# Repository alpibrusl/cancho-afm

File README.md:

# cancho-afm

An atomic force microscope, and a high-speed one as the second goal, that **runs by itself**: the software is written in
[cancho](https://github.com/alpibrusl/cancho), the controller logic in [cancho-hdl](https://github.com/alpibrusl/cancho-hdl), the
operator interface in [cancho-ui](https://github.com/alpibrusl/cancho-ui), and the hardware is built only from open hardware.

> **Status: design. Nothing is built, nothing is measured, no part has been bought.** Everything in `docs/` is a plan or a
> reading of someone else's published work, marked as such. The build manual in `docs/manual/` is a **draft**: no step in it has
> been carried out by anyone yet, and each step says so until someone signs it off.

## What "automatic" means here

1. **Approach**: bring the tip to the surface without crashing it, with no operator at the knobs.
2. **Tune**: find the cantilever's resonance, choose the setpoint and the loop gains, and tell the operator what it chose.
3. **Scan**: raster a requested area, keep the feedback stable, stop and retract on a fault.
4. **Report**: write the image with every setting that made it, so a run can be repeated.

The safety rule of `cancho-robot` carries over: the part that can damage the instrument (the Z drive and the approach motor) sits
behind a limit and a deadman that live in hardware, so a software fault cannot drive the tip into the sample.

## Layout

| Path | What |
|---|---|
| `docs/design.md` | the architecture, what is automatic, the safety model, the slices |
| `docs/open-hardware-policy.md` | what "open hardware only" means for this project and what it excludes |
| `docs/references.md` | the open AFM/SPM projects this builds on, read from search results, not verified |
| `docs/manual/` | how to build the device (draft) |
| `docs/index.html` | the project page and the step-by-step tutorial |
| `docs/simulator.md`, `docs/host.md`, `docs/registers.md` | the software twin, the host program, the board's register map |
| `docs/amplifier.md`, `hw/amp/` | the amplifier design and its ngspice simulations |
| `docs/first-hardware.md`, `bench/` | the first run on the real board |
| `docs/cost.md`, `docs/buy-now.md` | what build one costs for France and Spain, and what to order now |
| `gen/`, `sim/`, `host/`, `tests/` | the generated hardware, the models, the host program and their tests; `sh test_all.sh` runs all of it |

Open questions are issues in this repository.

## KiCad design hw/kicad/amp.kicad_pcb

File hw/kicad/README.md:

# hw/kicad: the piezo driver board

`amp.kicad_sch` is the schematic of the X, Y and Z piezo drivers, the 1.43 V reference, the supply and the fork's front end (drive divider, C0 trimmer, transimpedance stage, gain about 1.65 V, ADC clamp) of [`docs/amplifier.md`](../../docs/amplifier.md), **generated** by `gen_sch.cho`
(`cancho run hw/kicad/gen_sch.cho --std > hw/kicad/amp.kicad_sch`). It is written like a netlist: every pin ends in a net label, so the nets are the names in the generator and nothing depends on
placement. The symbols are the generator's own (library `cancho`, embedded in the file); the footprints are the parts to buy, **not checked against their pad numbering**.

`sh hw/kicad/check.sh` (with `CANCHO` and, for the KiCad part, `KICAD_CLI`) checks: the file equals the generator's output; KiCad's ERC (10.0.7) has no finding except the library
configuration of the machine; and `check_nets.py` reads the exported netlist and confirms, for X, Y and Z, that Rf is taken from the load side, Cf from the op-amp output, Riso in series, the
op-amp pins, the values **equal those of `hw/amp/xy_amp_b.cir` and `z_amp.cir`**, the reference divider can hold 1.43 V, and the decoupling is there.

The 48 checks include the fork front end's values against `hw/amp/fork_fe.cir`, and each of three deliberate breaks (a wrong value, swapped op-amp inputs, a clamp to the wrong rail) is caught. **Not done:** no board layout; the front end is on the same ±12 V rails as the drivers (the ADC clamp, not the rail, protects the converter); no layout guard around the 1 Mohm node; part values are those
of the simulation (the piezo's capacitance and the op-amp's output resistance are still assumptions). The first check found a real error: `z_amp.cir` carried Cf = 330 pF while the design and
the document's table use 680 pF; the file is corrected.

## The board (`amp.kicad_pcb`): placed and routed, in cancho

`sh hw/kicad/make_pcb.sh > hw/kicad/amp.kicad_pcb` (with `CANCHO` and `KICAD_CLI`) makes the board end to end:

1. `gen_pcb.py` (Python, standard library only) reads the netlist exported from the schematic, copies each footprint it names from KiCad's own libraries, puts the 69 parts in rows by function, draws a 141 x 121 mm outline and a ground
   pour (solid connections) on both layers, and writes the pads to `/tmp/amprouter/pads.txt`;
2. **`route.cho` routes it, in cancho; no Java, no Freerouting.** A 127 um grid on two layers; each net grows as a tree, one pad at a time, by a shortest-path search (Dijkstra with a penalty for going against a layer's preferred
   direction and for a via) to the nearest pad it has not joined; routed copper and pads become keep-out disks for the other nets (track 0.25 mm, clearance 0.2 mm, via 0.8 mm / 0.4 mm drill, plus a cell for the snapping of
   centres to the grid). Ground is routed like the others (a pour alone left islands that KiCad reports as unconnected), and the pour is added on top. No rip-up: a blocked net is reported (`F n`) and left, so the answer is a partial routing, never a short. It runs in about 3 seconds;
3. `gen_pcb.py` adds the tracks and vias to the board.

**Result (KiCad 10.0.7 DRC, with refilled zones):** every net routed, ground included as well as poured (45 vias, from 55 in the first version; power tracks 0.5 mm; the 1 Mohm node's copper is routed early and its pads and tracks carry a 0.9 mm keep-out for other copper), **0 unconnected, 0 clearance, 0 shorting findings, 0 schematic-parity errors**; the only findings are 69 about the machine's library
configuration, ignored by `check.sh`. A deliberate short added to a copy is reported (5 shorting items), and a wrong pad net raises the parity errors, so the check can fail. Two first runs showed what the router's model got wrong,
and the fixes are in the source: pad keep-outs ignored the snapping of centres to the grid (clearance 0.17 mm against 0.2 mm), and a square pad reaches its corner, not its half-width.

**The 1 Mohm node (TIN), measured on the routed board, not gated:** the smallest gap between its copper and any other net's copper is **0.43 mm**, not the 0.9 mm asked for. The keep-out works one way (other nets keep 0.9 mm from TIN's tracks and pads), but TIN's own tracks were only kept the ordinary 0.2 mm from other nets' pads, and those pads set the 0.43 mm. It is a keep-out plus the ground pour around it, **not a driven guard ring**. Do not read it as leakage-safe: that needs a guard at the input potential (here a virtual ground, so ground itself) and a clean board.

**Not done, and not claimed:** the placement is a first arrangement, not an optimised one (45 vias is still a lot; the op-amps' decoupling loops are not short by design; the piezo outputs are not kept away
from the fork input); the tracks are 90 degrees (no 45-degree corners), power tracks 0.5 mm and the rest 0.25 mm; no mounting holes or silkscreen text; no fabrication check (a fab's own rules, the stack-up, annular ring, drill sizes); and the
board has never been built or measured.

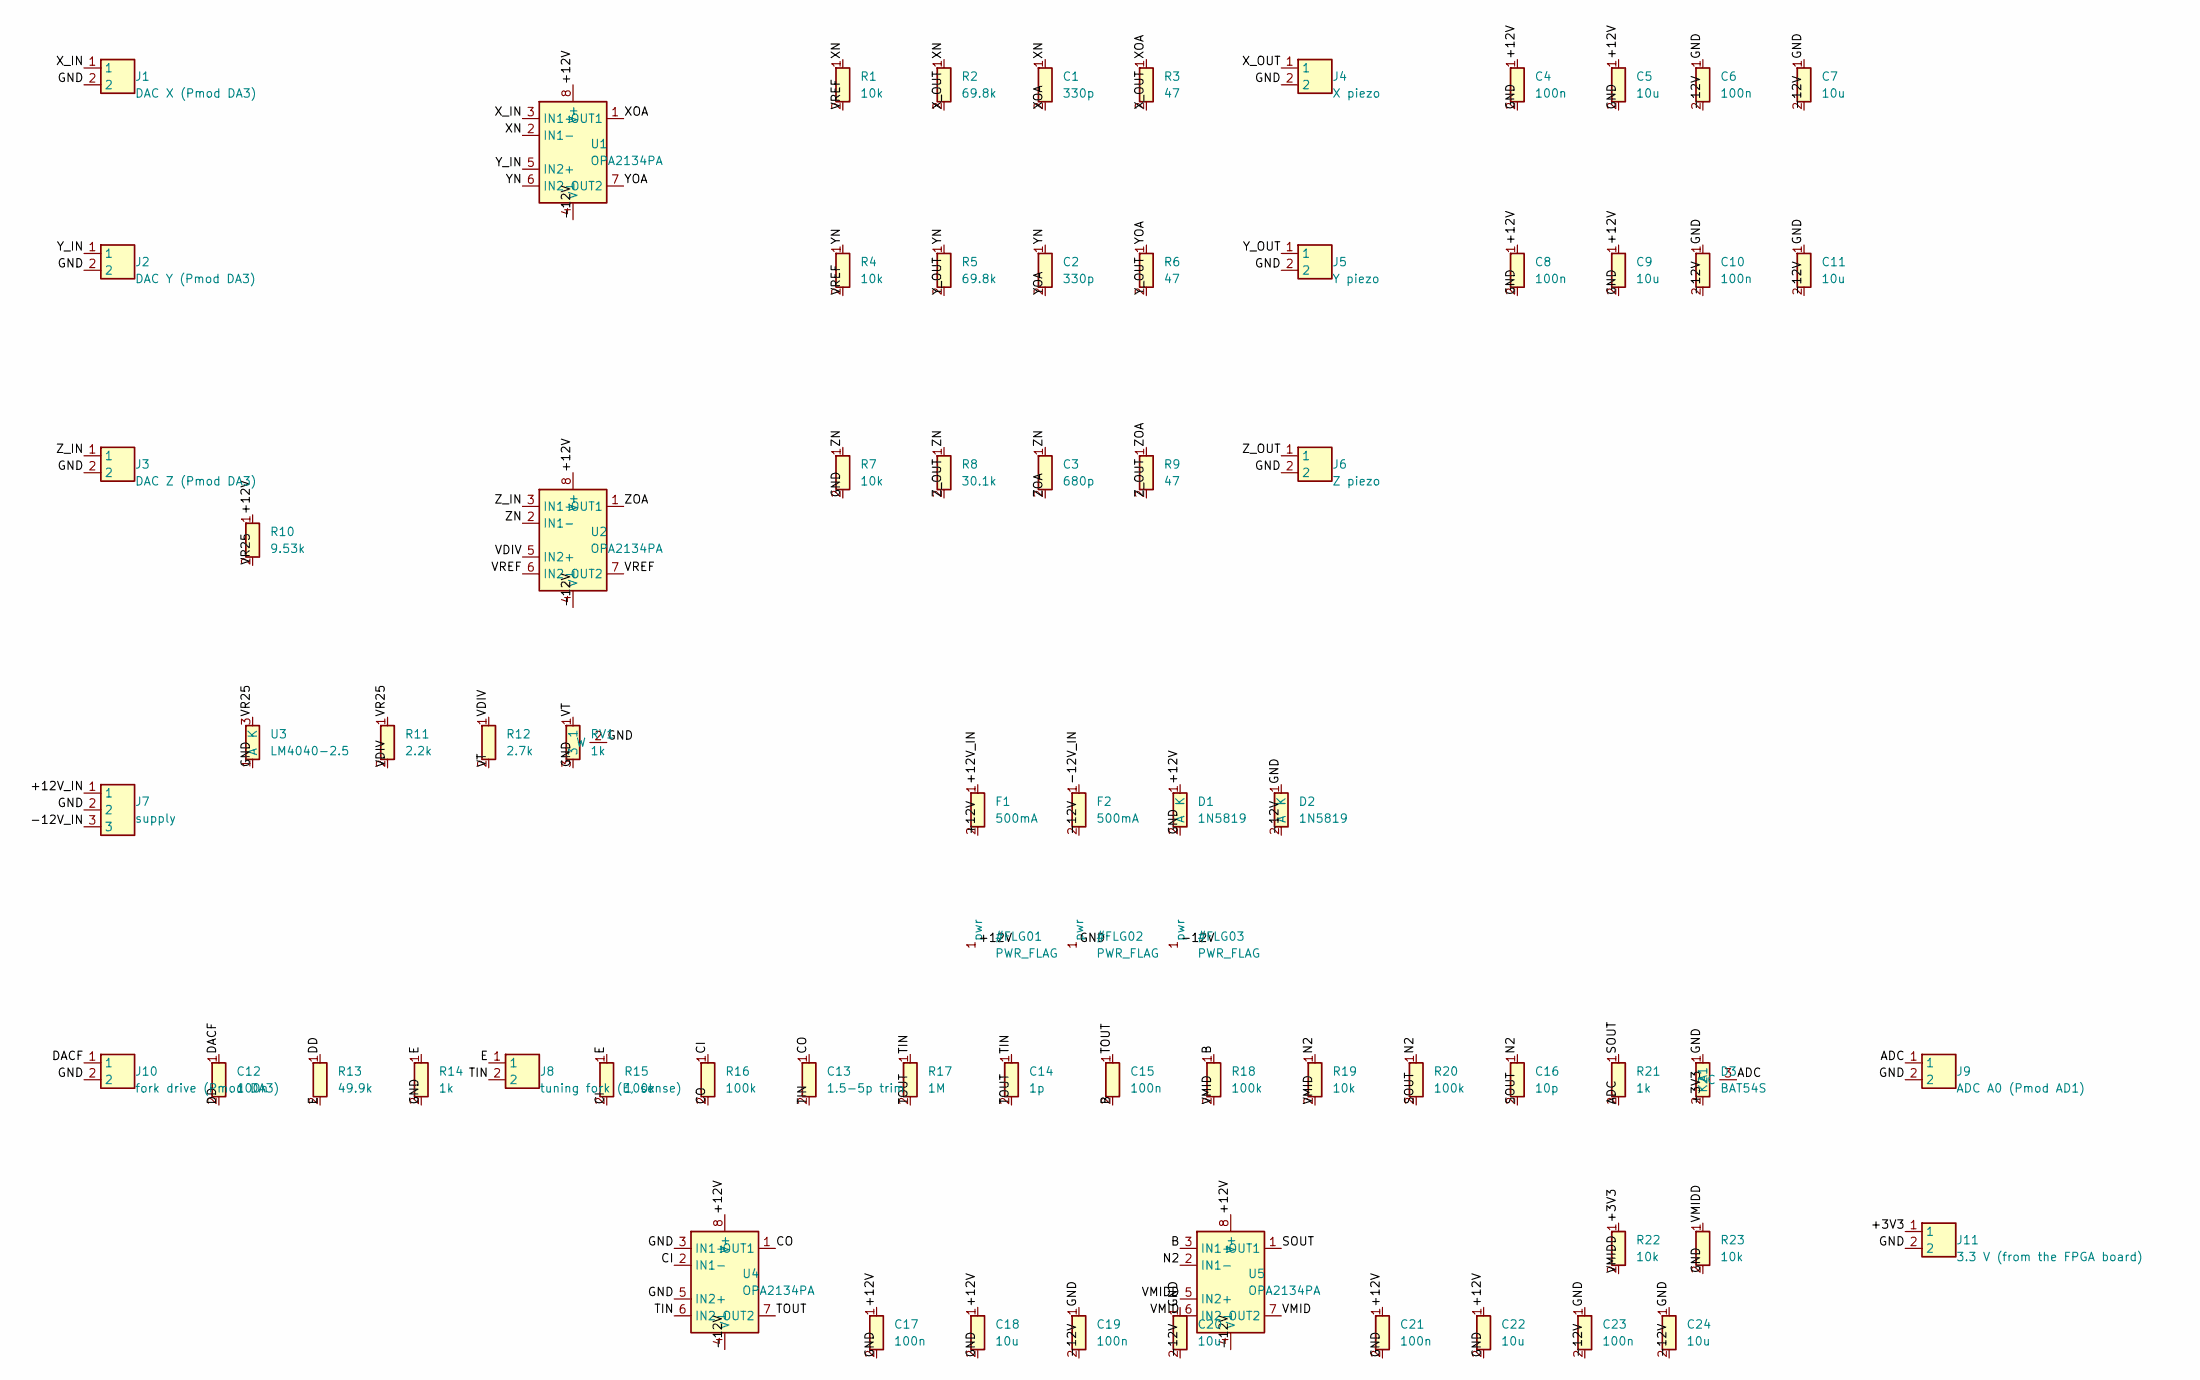
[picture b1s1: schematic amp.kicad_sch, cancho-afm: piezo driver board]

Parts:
C1, C2: 330p; C_Disc_D5.0mm_W2.5mm_P5.00mm
C3: 680p; C_Disc_D5.0mm_W2.5mm_P5.00mm
C4, C6, C8, C10, C17, C19, C21, C23: 100n; C_Disc_D5.0mm_W2.5mm_P5.00mm
C5, C7, C9, C11, C18, C20, C22, C24: 10u; C_Disc_D6.0mm_W4.4mm_P5.00mm
C12, C15: 100n; C_Rect_L7.2mm_W3.0mm_P5.00mm_FKS2_FKP2_MKS2_MKP2
C13: 1.5-5p trim; C_Disc_D5.0mm_W2.5mm_P5.00mm
C14: 1p; C_Disc_D5.0mm_W2.5mm_P5.00mm
C16: 10p; C_Disc_D5.0mm_W2.5mm_P5.00mm
D1, D2: 1N5819; D_DO-41_SOD81_P10.16mm_Horizontal
D3: BAT54S; SOT-23
F1, F2: 500mA; Fuse_1206_3216Metric
J1: DAC X (Pmod DA3); PinHeader_1x02_P2.54mm_Vertical
J2: DAC Y (Pmod DA3); PinHeader_1x02_P2.54mm_Vertical
J3: DAC Z (Pmod DA3); PinHeader_1x02_P2.54mm_Vertical
J4: X piezo; PinHeader_1x02_P2.54mm_Vertical
J5: Y piezo; PinHeader_1x02_P2.54mm_Vertical
J6: Z piezo; PinHeader_1x02_P2.54mm_Vertical
J7: supply; PinHeader_1x03_P2.54mm_Vertical
J8: tuning fork (E, sense); PinHeader_1x02_P2.54mm_Vertical
J9: ADC A0 (Pmod AD1); PinHeader_1x02_P2.54mm_Vertical
J10: fork drive (Pmod DA3); PinHeader_1x02_P2.54mm_Vertical
J11: 3.3 V (from the FPGA board); PinHeader_1x02_P2.54mm_Vertical
R1, R4, R7, R19, R22, R23: 10k; R_Axial_DIN0207_L6.3mm_D2.5mm_P10.16mm_Horizontal
R2, R5: 69.8k; R_Axial_DIN0207_L6.3mm_D2.5mm_P10.16mm_Horizontal
R3, R6, R9: 47; R_Axial_DIN0207_L6.3mm_D2.5mm_P10.16mm_Horizontal
R8: 30.1k; R_Axial_DIN0207_L6.3mm_D2.5mm_P10.16mm_Horizontal
R10: 9.53k; R_Axial_DIN0207_L6.3mm_D2.5mm_P10.16mm_Horizontal
R11: 2.2k; R_Axial_DIN0207_L6.3mm_D2.5mm_P10.16mm_Horizontal
R12: 2.7k; R_Axial_DIN0207_L6.3mm_D2.5mm_P10.16mm_Horizontal
R13: 49.9k; R_Axial_DIN0207_L6.3mm_D2.5mm_P10.16mm_Horizontal
R14, R21: 1k; R_Axial_DIN0207_L6.3mm_D2.5mm_P10.16mm_Horizontal
R15, R16, R18, R20: 100k; R_Axial_DIN0207_L6.3mm_D2.5mm_P10.16mm_Horizontal
R17: 1M; R_Axial_DIN0207_L6.3mm_D2.5mm_P10.16mm_Horizontal
RV1: 1k; Potentiometer_Bourns_3296W_Vertical
U1, U2, U4, U5: OPA2134PA; DIP-8_W7.62mm
U3: LM4040-2.5; SOT-23

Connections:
/+3V3: D3.2 (K2), J11.1, R22.1
/+12V: C4.1, C5.1, C8.1, C9.1, C17.1, C18.1, C21.1, C22.1, D1.1 (K), F1.2, R10.1, U1.8 (V+), U2.8 (V+), U4.8 (V+), U5.8 (V+)
/+12V_IN: F1.1, J7.1
/-12V: C6.2, C7.2, C10.2, C11.2, C19.2, C20.2, C23.2, C24.2, D2.2 (A), F2.2, U1.4 (V-), U2.4 (V-), U4.4 (V-), U5.4 (V-)
/-12V_IN: F2.1, J7.3
/ADC: D3.3 (C), J9.1, R21.2
/B: C15.2, R18.1, U5.3 (IN1+)
/CI: R15.2, R16.1, U4.2 (IN1-)
/CO: C13.1, R16.2, U4.1 (OUT1)
/DACF: C12.1, J10.1
/DD: C12.2, R13.1
/E: J8.1, R13.2, R14.1, R15.1
/GND: C4.2, C5.2, C6.1, C7.1, C8.2, C9.2, C10.1, C11.1, C17.2, C18.2, C19.1, C20.1, C21.2, C22.2, C23.1, C24.1, D1.2 (A), D2.1 (K), D3.1 (A1), J1.2, J2.2, J3.2, J4.2, J5.2, J6.2, J7.2, J9.2, J10.2, J11.2, R7.2, R14.2, R23.2, RV1.2 (W), RV1.3, U3.1 (A), U4.3 (IN1+), U4.5 (IN2+)
/N2: C16.1, R19.1, R20.1, U5.2 (IN1-)
/SOUT: C16.2, R20.2, R21.1, U5.1 (OUT1)
/TIN: C13.2, C14.1, J8.2, R17.1, U4.6 (IN2-)
/TOUT: C14.2, C15.1, R17.2, U4.7 (OUT2)
/VDIV: R11.2, R12.1, U2.5 (IN2+)
/VMID: R18.2, R19.2, U5.6 (IN2-), U5.7 (OUT2)
/VMIDD: R22.2, R23.1, U5.5 (IN2+)
/VR25: R10.2, R11.1, U3.3 (K)
/VREF: R1.2, R4.2, U2.6 (IN2-), U2.7 (OUT2)
/VT: R12.2, RV1.1
/XN: C1.1, R1.1, R2.1, U1.2 (IN1-)
/XOA: C1.2, R3.1, U1.1 (OUT1)
/X_IN: J1.1, U1.3 (IN1+)
/X_OUT: J4.1, R2.2, R3.2
/YN: C2.1, R4.1, R5.1, U1.6 (IN2-)
/YOA: C2.2, R6.1, U1.7 (OUT2)
/Y_IN: J2.1, U1.5 (IN2+)
/Y_OUT: J5.1, R5.2, R6.2
/ZN: C3.1, R7.1, R8.1, U2.2 (IN1-)
/ZOA: C3.2, R9.1, U2.1 (OUT1)
/Z_IN: J3.1, U2.3 (IN1+)
/Z_OUT: J6.1, R8.2, R9.2

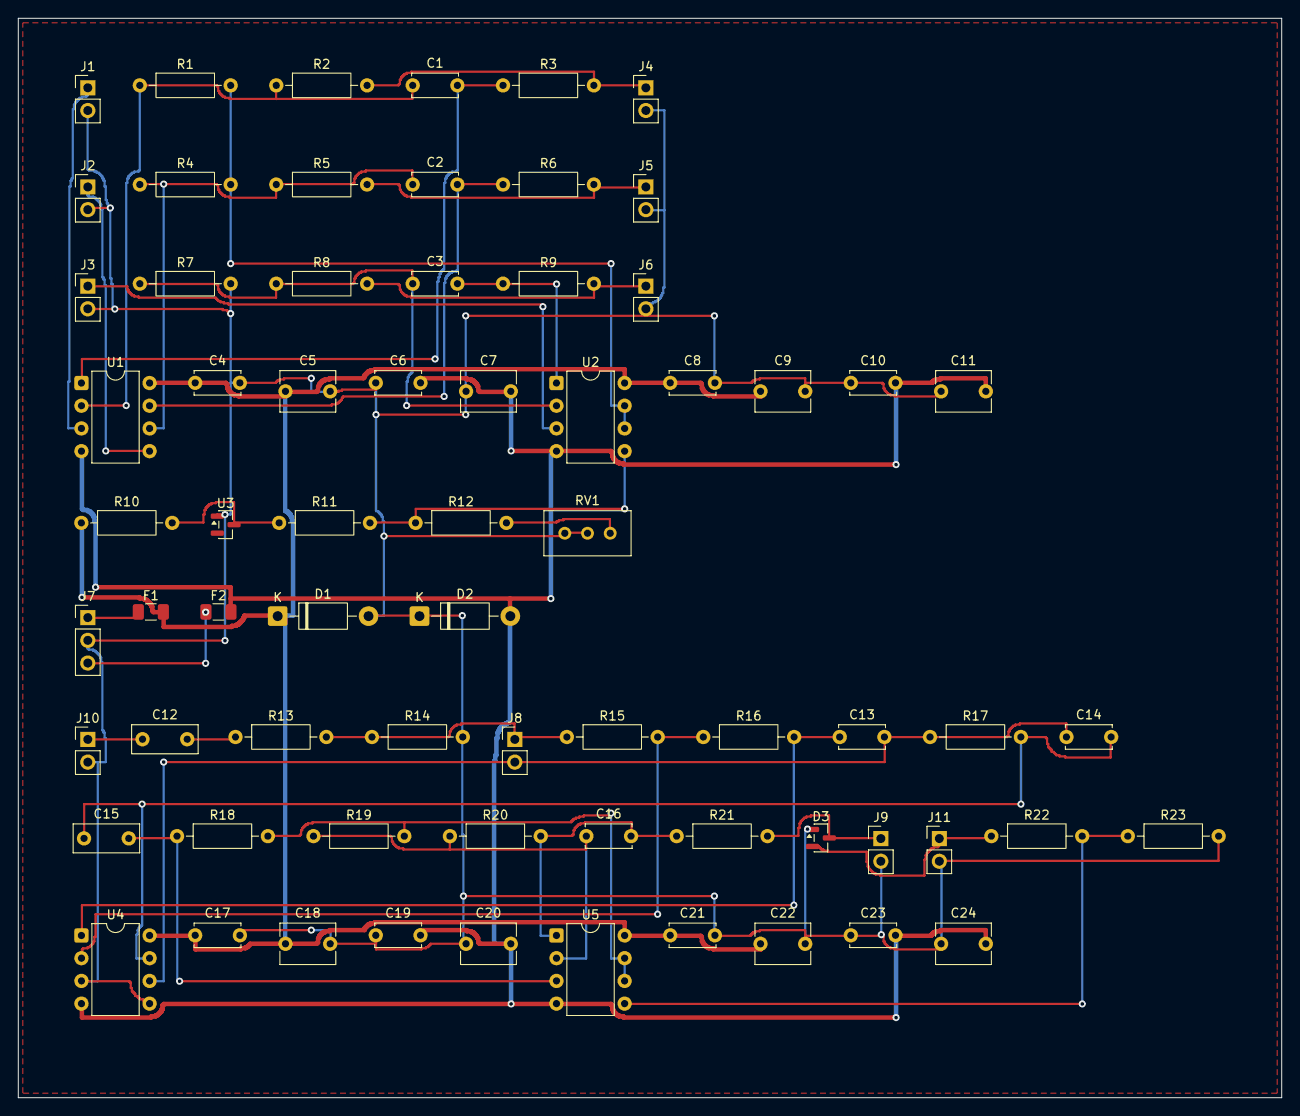
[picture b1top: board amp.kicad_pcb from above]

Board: 2 copper layers, 141.3 x 120.7 mm, 69 parts (0 on the bottom side), 35 nets.

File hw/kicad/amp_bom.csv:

value,footprint,quantity,references,what to buy
330p,C_Disc_D5.0mm_W2.5mm_P5.00mm,2,C1 C2,"ceramic C0G/NP0, 50 V, 5 mm pitch (the compensation capacitors set the amplifier's stability: not X7R)"
680p,C_Disc_D5.0mm_W2.5mm_P5.00mm,1,C3,"ceramic C0G/NP0, 50 V, 5 mm pitch (as above)"
100n,C_Disc_D5.0mm_W2.5mm_P5.00mm,8,C4 C6 C8 C10 C17 C19 C21 C23,"ceramic X7R, 50 V, 5 mm pitch (decoupling)"
10u,C_Disc_D6.0mm_W4.4mm_P5.00mm,8,C5 C7 C9 C11 C18 C20 C22 C24,"radial multilayer ceramic 10 uF, X7R, 25 V or more, 5 mm pitch, NOT polarised (the -12 V rail reverses the sense an electrolytic needs)"
100n,C_Rect_L7.2mm_W3.0mm_P5.00mm_FKS2_FKP2_MKS2_MKP2,2,C12 C15,"film (PET/PP) 100 nF, 63 V or more, 5 mm pitch (signal coupling in the fork path)"
1.5-5p trim,C_Disc_D5.0mm_W2.5mm_P5.00mm,1,C13,"trimmer capacitor 1.5-5 pF, through hole (the footprint is a PLACEHOLDER: take the pitch from the part's datasheet)"
1p,C_Disc_D5.0mm_W2.5mm_P5.00mm,1,C14,"ceramic C0G/NP0, 50 V, 5 mm pitch, +-0.25 pF or better"
10p,C_Disc_D5.0mm_W2.5mm_P5.00mm,1,C16,"ceramic C0G/NP0, 50 V, 5 mm pitch"
1N5819,D_DO-41_SOD81_P10.16mm_Horizontal,2,D1 D2,"Schottky diode 1 A, DO-41 (reverse-supply protection, across the rails)"
BAT54S,SOT-23,1,D3,"BAT54S dual series Schottky, SOT-23 (surface mount)"
500mA,Fuse_1206_3216Metric,2,F1 F2,"fuse or resettable PTC 500 mA, 1206 (surface mount)"
header,PinHeader_1x02_P2.54mm_Vertical,10,J1 J2 J3 J4 J5 J6 J8 J9 J10 J11,"pin header 2.54 mm, 2 pins (a piezo or DAC lead, or a screw terminal of the same pitch)"
header,PinHeader_1x03_P2.54mm_Vertical,1,J7,"pin header 2.54 mm, 3 pins (a piezo or DAC lead, or a screw terminal of the same pitch)"
10k,R_Axial_DIN0207_L6.3mm_D2.5mm_P10.16mm_Horizontal,6,R1 R4 R7 R19 R22 R23,"metal film 1 %, 0207"
69.8k,R_Axial_DIN0207_L6.3mm_D2.5mm_P10.16mm_Horizontal,2,R2 R5,"metal film 1 %, 0207 (E96 value: it sets the X/Y gain 7.98)"
47,R_Axial_DIN0207_L6.3mm_D2.5mm_P10.16mm_Horizontal,3,R3 R6 R9,"metal film 1 %, 0207"
30.1k,R_Axial_DIN0207_L6.3mm_D2.5mm_P10.16mm_Horizontal,1,R8,"metal film 1 %, 0207 (E96 value: it sets the Z gain 4.01)"
9.53k,R_Axial_DIN0207_L6.3mm_D2.5mm_P10.16mm_Horizontal,1,R10,"metal film 1 %, 0207 (E96 value)"
2.2k,R_Axial_DIN0207_L6.3mm_D2.5mm_P10.16mm_Horizontal,1,R11,"metal film 1 %, 0207"
2.7k,R_Axial_DIN0207_L6.3mm_D2.5mm_P10.16mm_Horizontal,1,R12,"metal film 1 %, 0207"
49.9k,R_Axial_DIN0207_L6.3mm_D2.5mm_P10.16mm_Horizontal,1,R13,"metal film 1 %, 0207 (E96 value: the fork drive divider 1/50.9)"
1k,R_Axial_DIN0207_L6.3mm_D2.5mm_P10.16mm_Horizontal,2,R14 R21,"metal film 1 %, 0207"
100k,R_Axial_DIN0207_L6.3mm_D2.5mm_P10.16mm_Horizontal,4,R15 R16 R18 R20,"metal film 1 %, 0207"
1M,R_Axial_DIN0207_L6.3mm_D2.5mm_P10.16mm_Horizontal,1,R17,"metal film 1 %, 0207"
1k,Potentiometer_Bourns_3296W_Vertical,1,RV1,"multi-turn trimmer 1 k, Bourns 3296W style (sets VREF to 1.43 V)"
OPA2134PA,DIP-8_W7.62mm,4,U1 U2 U4 U5,"OPA2134PA dual FET op-amp, DIP-8 (the simulation's reference)"
LM4040-2.5,SOT-23,1,U3,"LM4040 2.5 V shunt reference, SOT-23 (surface mount); B grade (0.2 %) or better"

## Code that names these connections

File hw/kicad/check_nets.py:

"""Checks hw/kicad/amp.kicad_sch against the circuits that were simulated (hw/amp/xy_amp_b.cir, z_amp.cir).
Input: the KiCad netlist (kicad-cli sch export netlist --format kicadsexpr). Prints one line per check; exits 1 if any fails."""
import re, sys

def sexp(text):
    tok = re.findall(r'\(|\)|"(?:[^"\\]|\\.)*"|[^\s()]+', text)
    pos = 0
    def parse():
        nonlocal pos
        pos += 1
        out = []
        while tok[pos] != ')':
            if tok[pos] == '(':
                out.append(parse())
            else:
                out.append(tok[pos].strip('"'))
                pos += 1
        pos += 1
        return out
    return parse()

def find(node, name):
    return [c for c in node if isinstance(c, list) and c and c[0] == name]

net = sexp(open(sys.argv[1]).read())
parts = {}
for c in find(find(net, 'components')[0], 'comp'):
    ref = find(c, 'ref')[0][1]
    parts[ref] = find(c, 'value')[0][1]
pin_net = {}
for n in find(find(net, 'nets')[0], 'net'):
    name = find(n, 'name')[0][1].lstrip('/')
    for nd in find(n, 'node'):
        pin_net[(find(nd, 'ref')[0][1], find(nd, 'pin')[0][1])] = name

fails = 0
def check(ok, what):
    global fails
    print(("PASS " if ok else "FAIL ") + what)
    if not ok: fails += 1

def between(ref, a, b):
    return {pin_net.get((ref, '1')), pin_net.get((ref, '2'))} == {a, b}

def spice(path):
    d = {}
    for line in open(path):
        m = re.match(r'^(Rg|Rf|Riso)\s+\S+\s+\S+\s+(\S+)', line)
        if m: d[m.group(1)] = m.group(2)
        m = re.search(r'\.param.*\bCF=(\S+)', line)
        if m: d['Cf'] = m.group(1)
        m = re.search(r'\bRISO=(\S+)', line)
        if m: d['Riso'] = m.group(1)
    return d

xy, z = spice('../amp/xy_amp_b.cir'), spice('../amp/z_amp.cir')
# channel: (name, Rg, Rf, Cf, Riso, Rg returns to, op-amp, inverting pin, output pin, non-inverting pin, input net, out net)
chans = [('X', 'R1', 'R2', 'C1', 'R3', 'VREF', 'U1', '2', '1', '3', 'X_IN', 'X_OUT', 'XN', 'XOA', xy),
         ('Y', 'R4', 'R5', 'C2', 'R6', 'VREF', 'U1', '6', '7', '5', 'Y_IN', 'Y_OUT', 'YN', 'YOA', xy),
         ('Z', 'R7', 'R8', 'C3', 'R9', 'GND', 'U2', '2', '1', '3', 'Z_IN', 'Z_OUT', 'ZN', 'ZOA', z)]
for (n, rg, rf, cf, ri, rto, u, minus, outp, plus, vin, vout, inn, oa, sp) in chans:
    check(between(rg, inn, rto), f"{n}: Rg {rg} joins the inverting node {inn} to {rto}")
    check(between(rf, inn, vout), f"{n}: Rf {rf} is taken from the LOAD side ({vout}), not the op-amp output")
    check(between(cf, inn, oa), f"{n}: Cf {cf} joins {inn} to the op-amp output {oa}")
    check(between(ri, oa, vout), f"{n}: Riso {ri} joins the op-amp output {oa} to {vout}")
    check(pin_net.get((u, minus)) == inn and pin_net.get((u, outp)) == oa and pin_net.get((u, plus)) == vin, f"{n}: {u} pins {minus}/{outp}/{plus} are {inn}/{oa}/{vin}")
    check(parts[rg] == sp['Rg'] and parts[rf] == sp['Rf'] and parts[cf] == sp['Cf'] and parts[ri] in (sp['Riso'], '47'),
          f"{n}: values Rg {parts[rg]} Rf {parts[rf]} Cf {parts[cf]} Riso {parts[ri]} equal the simulation's {sp['Rg']} {sp['Rf']} {sp['Cf']} {sp['Riso']}")
# the reference buffer: a follower on VREF
check(pin_net.get(('U2', '5')) == 'VDIV' and pin_net.get(('U2', '6')) == 'VREF' and pin_net.get(('U2', '7')) == 'VREF', "VREF: U2 unit 2 is a follower of VDIV")
# the divider from the 2.5 V shunt: unloaded output with the trimmer at mid-travel (500 ohm), computed from the schematic's own values
def ohms(s):
    m = re.match(r'^([0-9.]+)(k?)$', s)
    return float(m.group(1)) * (1000 if m.group(2) else 1)
rt, rb, rv = ohms(parts['R11']), ohms(parts['R12']), ohms(parts['RV1'])
vlo, vhi = 2.5 * rb / (rt + rb + rv), 2.5 * (rb + rv) / (rt + rb + rv)
check(vlo < 1.43 < vhi, f"VREF: the trimmer spans {vlo:.3f} to {vhi:.3f} V and holds the simulated 1.43 V")
check(between('R11', 'VR25', 'VDIV') and between('R12', 'VDIV', 'VT') and pin_net.get(('RV1', '1')) == 'VT' and pin_net.get(('RV1', '3')) == 'GND' and pin_net.get(('RV1', '2')) == 'GND', "VREF: R11, R12 and the rheostat form the divider VR25 - VDIV - VT - GND")
# every op-amp is decoupled on both rails
for c, a, b in [('C4', '+12V', 'GND'), ('C5', '+12V', 'GND'), ('C6', 'GND', '-12V'), ('C7', 'GND', '-12V')]:
    check(between(c, a, b), f"decoupling {c} {parts[c]} between {a} and {b}")

# ---- the fork's front end against hw/amp/fork_fe.cir ----
fe = {}
for line in open('../amp/fork_fe.cir'):
    m = re.match(r'^(Cc|Rd1|Rd2|Rc1|Rc2|Rf|Cfb|Cc2|Rb|Rg2|Rf2|Cf2|Rs)\s+\S+\s+\S+\s+(\S+)', line)
    if m: fe[m.group(1)] = m.group(2)
    m = re.search(r'\.param.*\bRF=(\S+).*\bCFB=(\S+)', line)
    if m: fe['Rf'], fe['Cfb'] = m.group(1), m.group(2)
def norm(v):
    v = v.replace('Meg', 'M')
    return {'{RF}': '1M', '{CFB}': '1p'}.get(v, v)
spice_ref = {'Cc': 'C12', 'Rd1': 'R13', 'Rd2': 'R14', 'Rc1': 'R15', 'Rc2': 'R16', 'Rf': 'R17', 'Cfb': 'C14', 'Cc2': 'C15', 'Rb': 'R18', 'Rg2': 'R19', 'Rf2': 'R20', 'Cf2': 'C16', 'Rs': 'R21'}
for k, ref in spice_ref.items():
    want = {'Rf': '1M', 'Cfb': '1p'}.get(k, norm(fe.get(k, '?')))
    check(parts[ref] == want, f"fork front end: {ref} ({k}) is {parts[ref]}, the simulation's {want}")
check(between('C12', 'DACF', 'DD') and between('R13', 'DD', 'E') and between('R14', 'E', 'GND'), "fork front end: drive Cc - Rd1 - E - Rd2 - GND")
check(between('R15', 'E', 'CI') and between('R16', 'CI', 'CO') and between('C13', 'CO', 'TIN'), "fork front end: C0 compensation E - inverter - trimmer - TIN")
check(pin_net.get(('U4', '3')) == 'GND' and pin_net.get(('U4', '2')) == 'CI' and pin_net.get(('U4', '1')) == 'CO', "fork front end: U4 unit 1 is the inverter (CI -> CO)")
check(pin_net.get(('U4', '5')) == 'GND' and pin_net.get(('U4', '6')) == 'TIN' and pin_net.get(('U4', '7')) == 'TOUT', "fork front end: U4 unit 2 is the transimpedance stage (TIN -> TOUT)")
check(between('R17', 'TIN', 'TOUT') and between('C14', 'TIN', 'TOUT'), "fork front end: 1 Mohm || 1 pF across the transimpedance stage")
check(between('C15', 'TOUT', 'B') and between('R18', 'B', 'VMID') and between('R19', 'N2', 'VMID') and between('R20', 'N2', 'SOUT') and between('C16', 'N2', 'SOUT'), "fork front end: AC coupling, gain 11 about VMID")
check(pin_net.get(('U5', '3')) == 'B' and pin_net.get(('U5', '2')) == 'N2' and pin_net.get(('U5', '1')) == 'SOUT', "fork front end: U5 unit 1 is the gain stage")
check(pin_net.get(('U5', '5')) == 'VMIDD' and pin_net.get(('U5', '6')) == 'VMID' and pin_net.get(('U5', '7')) == 'VMID', "fork front end: U5 unit 2 buffers the 1.65 V middle")
check(between('R22', '+3V3', 'VMIDD') and between('R23', 'VMIDD', 'GND') and parts['R22'] == parts['R23'], "fork front end: VMID is half of 3.3 V")
check(between('R21', 'SOUT', 'ADC') and pin_net.get(('D3', '1')) == 'GND' and pin_net.get(('D3', '2')) == '+3V3' and pin_net.get(('D3', '3')) == 'ADC', "fork front end: 1 kohm and the BAT54S clamp (ADC to 3V3 and GND) protect the ADC input")
print("%d failure(s)" % fails)
sys.exit(1 if fails else 0)
